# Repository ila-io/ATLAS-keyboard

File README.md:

# ATLAS-keyboard
A custom low profile split keyboard designed for hack club highway! It has 33 keys on each side for a total of 66, and uses one these awesome open source [mouse wheel style encoders](https://github.com/Taro-Hayashi/THQWGD0010) by Taro Hayashi on each side for navigating text (they act as arrow keys, with the one on the left as an up and down, and the one on the right is left and right). The case also has a super minimal and low profile plateless design with no top frame that leaves the cool part of the PCB uncovered, and keeps the keys nice and low on my desk. It also features a system for creating adjustable tenting angles, which is nice because I'd like to find what works best for me comfort-wise! 
i named it atlas becasue umm uhh it'll help me with text navigation? (ok this is a stretch, i just like the word) 

# Overview
In exploring split keyboard layouts, I found that not many of them had all the keys that I wanted, and the ones that did had crazy layouts and sizes. I struck a balance between the two, minimizing the size of my keyboard by making it as low profile as possible and limiting it to only the keys that I wanted.

### NOTE:
PCB designs are based off of the PCB files/config.yaml Ergogen file, schematics are only used as reference.

## BOM 

|Item                                  |Count|Total Cost|Source     |Link                                                                 |Notes                                                                                       |
|--------------------------------------|-----|----------|-----------|---------------------------------------------------------------------|--------------------------------------------------------------------------------------------|
|Choc 1u Keycaps x10                   |6    |$21.00    |typeractive|https://typeractive.xyz/products/mbk-keycaps?variant=45419753111783  |                                                                                            |
|Choc 1.5u Keycaps x2                  |6    |$9.00     |typeractive|https://typeractive.xyz/products/mbk-keycaps?variant=48512019333351  |                                                                                            |
|Choc v1 Red Switches x10              |8    |$44       |typeractive|https://typeractive.xyz/products/choc-switches?variant=45741919240423|A little more expensive than some alternatives, but free shipping brings it below all others|
|Kailh Low Profile Hotswap Sockets x100|1    |$0.99     |aliexpress |https://www.aliexpress.us/item/3256803389452947.html                 |First time discount                                                                         |
|1N4148W SMD Diodes x100               |1    |$1.37     |aliexpress |https://www.aliexpress.com/item/3256806137153769.html                |                                                                                            |
|M2x6mm screws x50                     |1    |$1.74     |aliexpress |https://www.aliexpress.com/item/2255801062616407.html?mp=1           |                                                                                            |
|M2 Hex Nuts x50                       |1    |$1.51     |aliexpress |https://www.aliexpress.com/item/3256807407546447.html?mp=1           |                                                                                            |
|6x6x7 Tactile Button Switch x100      |1    |$2.07     |aliexpress |https://www.aliexpress.com/item/3256803858853331.html?mp=1           |                                                                                            |
|11mm Mouse Encoder x10                |1    |$1.56     |aliexpress |https://www.aliexpress.com/item/3256801290854651.html?mp=1           |                                                                                            |
|left PCB x5 + right PCB x5 + shipping |1    |$29.65    |JLCPCB     |https://www.jlcpcb.com/                                              |                                                                                            |
|Atmega32U4 Pro Micro Board Module x3  |1    |$19.88    |amazon     |https://a.co/d/17oYyaQ                                               |even though there are 3 of them, when considering shipping this is the best deal i could find on even 2          |
|Total:                                |     |$132.77   |           |                                                                     |                                                                                            |

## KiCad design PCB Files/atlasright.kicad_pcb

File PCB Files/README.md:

# NOTE:
The .kicad_sch schematic files are for reference only, the PCB files are not directly pulled from them. They are generated by the config.yaml [ergogen](https://github.com/ergogen/ergogen) file

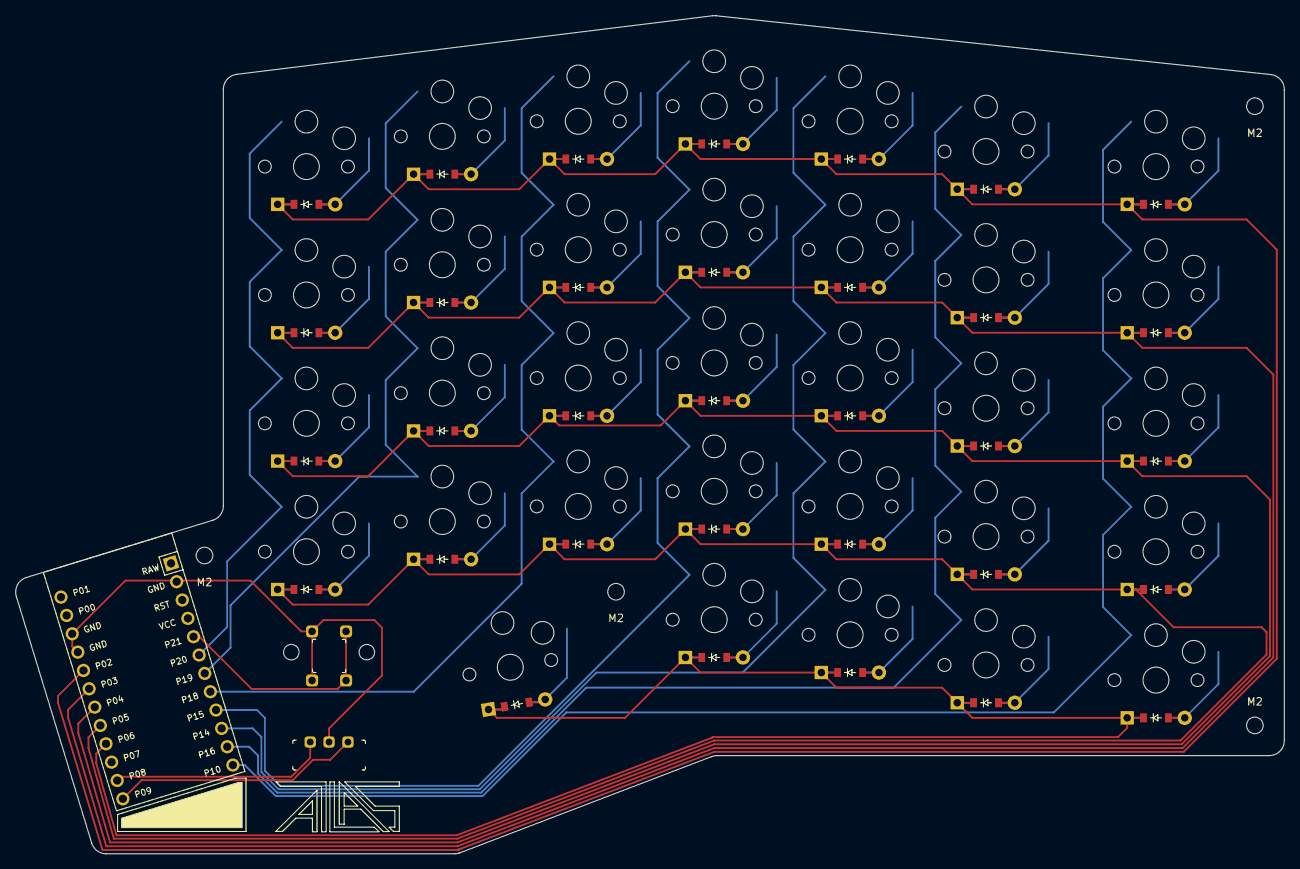
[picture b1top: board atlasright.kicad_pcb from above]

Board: 2 copper layers, 168.0 x 111.0 mm, 71 parts (0 on the bottom side), 46 nets.

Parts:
D1, D2, D3, D4, D5, D6, D7, D8, D9, D10, D11, D12, D13, D14, D15, D16, D17, D18, D19, D20, D21, D22, D23, D24, D25, D26, D27, D28, D29, D30, D31, D32, D33: ComboDiode
M2, M2#2, M2#3, M2#4: MountingHole_2.2mm_M2
MCU1: ProMicro
S1, S2, S3, S4, S5, S6, S7, S8, S9, S10, S11, S12, S13, S14, S15, S16, S17, S18, S19, S20, S21, S22, S23, S24, S25, S26, S27, S28, S29, S30, S31, S32, S33: PG1350

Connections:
GND: MCU1.2, MCU1.15, MCU1.16
P2: D5.1, D10.1, D15.1, D20.1, D24.1, D28.1, D32.1, MCU1.17
P3: D4.1, D9.1, D14.1, D19.1, D23.1, D27.1, D31.1, MCU1.18
P4: D3.1, D8.1, D13.1, D18.1, D22.1, D26.1, D30.1, MCU1.19
P5: D2.1, D7.1, D12.1, D17.1, D21.1, D25.1, D29.1, MCU1.20
P6: D1.1, D6.1, D11.1, D16.1, D33.1, MCU1.21
P10: MCU1.12, S1.1, S2.1, S3.1, S4.1, S5.1
P14: MCU1.10, S11.1, S12.1, S13.1, S14.1, S15.1
P15: MCU1.9, S16.1, S17.1, S18.1, S19.1, S20.1
P16: MCU1.11, S6.1, S7.1, S8.1, S9.1, S10.1
P18: MCU1.8, S21.1, S22.1, S23.1, S24.1, S33.1
P19: MCU1.7, S25.1, S26.1, S27.1, S28.1
P20: MCU1.6, S29.1, S30.1, S31.1, S32.1
mirror_default_default: D33.2, S33.2
mirror_index_bottom: D21.2, S21.2
mirror_index_home: D22.2, S22.2
mirror_index_numbers: D24.2, S24.2
mirror_index_top: D23.2, S23.2
mirror_inner2_bottom: D29.2, S29.2
mirror_inner2_home: D30.2, S30.2
mirror_inner2_numbers: D32.2, S32.2
mirror_inner2_top: D31.2, S31.2
mirror_inner_bottom: D25.2, S25.2
mirror_inner_home: D26.2, S26.2
mirror_inner_numbers: D28.2, S28.2
mirror_inner_top: D27.2, S27.2
mirror_middle_bottom: D17.2, S17.2
mirror_middle_home: D18.2, S18.2
mirror_middle_mod: D16.2, S16.2
mirror_middle_numbers: D20.2, S20.2
mirror_middle_top: D19.2, S19.2
mirror_outer_bottom: D2.2, S2.2
mirror_outer_home: D3.2, S3.2
mirror_outer_mod: D1.2, S1.2
mirror_outer_numbers: D5.2, S5.2
mirror_outer_top: D4.2, S4.2
mirror_pinky_bottom: D7.2, S7.2
mirror_pinky_home: D8.2, S8.2
mirror_pinky_mod: D6.2, S6.2
mirror_pinky_numbers: D10.2, S10.2
mirror_pinky_top: D9.2, S9.2
mirror_ring_bottom: D12.2, S12.2
mirror_ring_home: D13.2, S13.2
mirror_ring_mod: D11.2, S11.2
mirror_ring_numbers: D15.2, S15.2
mirror_ring_top: D14.2, S14.2

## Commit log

2025-07-02 add photos for journal
2025-07-03 upload a lot of files
2025-07-06 add firmware, readme, and f3d file
2025-07-06 Update photos
2025-07-07 add reference schematic files
2025-07-29 add STEP files for cad
